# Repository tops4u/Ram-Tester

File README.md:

# Ram-Tester
**Fast, open-source DIY tester for vintage DRAM/SRAM** — auto-detects the
chip type, runs every test, gives a clear good/bad in seconds.

[GPL v3] [Firmware 5.1.2] · C64 · Amiga · Atari · ST · Apple II · Spectrum

## What this project is
A fast, open-source DIY RAM tester for vintage RAM chips used in C64, Amiga, Atari, and other retro computers. Built around a 16MHz ATmega328P on a custom PCB, it tests memory thoroughly in seconds and supports a wide range of chip types with optional OLED feedback.

<br/>

**As featured on:**

- [***Jan Beta***](https://www.youtube.com/watch?v=iQYF2-FwuoI) (Aug 2026): "The best Arduino Tester (so far)"
- [***Adrians Digital Basement II***](https://youtu.be/9QQ8ZqHPRVQ?&t=2573) (May 2026): "This is freaking awesome"
- [***Hackaday***](https://hackaday.com/2025/12/08/cheap-and-aggressive-dram-chip-tester/) (Dec 2025): "Cheap and Aggressive DRAM Chip Tester"
- [***Elektor Magazine***](https://www.elektormagazine.com/news/open-source-diy-ram-tester) (Dec 2025): "Ram-Tester Is an Open-Source DIY Solution for Retro Computer RAM"

---

## Why this tester?
- **No chip knowledge needed** – Set the pin count via DIP switch — the tester auto-detects the chip type and runs all tests automatically. No selecting algorithms, no choosing the right socket, no menus, no datasheet lookups. Grab a chip, plug it in, get a result.
- **Fast** – Full test in under 8 seconds for a 41256. Test a whole tray of chips in minutes.
- **Thorough** – While other testers require you to choose between test modes, this one runs them all: March-B address decoder test, memory patterns, crosstalk, retention time, CAS-before-RAS refresh, fast page mode, static column mode, short detection (VCC, GND and pin-to-pin).
- **Practical** – Broken is broken. You get a clear good/bad result because a DRAM chip can't be repaired anyway.
- **Safe** – Short-circuit protection, current limiting via resettable fuse, short detection against VCC, GND and between pins. Self-test mode included.
- **Fully Open Source** – Hardware, firmware, schematics. No black box.

---

## Key features
| Feature | Benefit |
|---------|---------|
| 20-pin ZIP socket on board | Direct test of 256K × 4 and 1M × 4 ZIP DRAMs without an adapter |
| Optional ZIP/SOJ adapter | Adds 1M × 1 ZIP and 41256 ZIP support, plus SOJ sockets for 18- and 20-pin SOJ RAMs <sup>1)</sup> |
| Optional OLED display or LED blink codes | Full text feedback or minimal hardware setup |
| Self-test mode | Verify the hardware for defects like short circuits or broken solder joints |

<sup>1)</sup> The 1M × 1 ZIP pinout differs from the 256K × 4 / 1M × 4 ZIP pinout, so these chips cannot use the on-board ZIP socket. See [Supported DRAM types](#supported-dram-types-speed-with-current-firmware-version).

---

## Supported DRAM types (speed with current firmware version)

| Capacity | DIP | 20-pin ZIP | Static Column | Nibble Mode | Retention Time | Test Time |
|----------|-----|------------|---------------|-------------|----------------|-----------|
| 4 K × 1 | 4027 <sup>1)</sup> | – | – | – | 2 ms | 0.2 s |
| 16 K × 1 | 4816 | – | – | – | 2 ms | 0.7 s |
| 16 K × 1 | 4116 <sup>1)</sup> | – | – | – | 2 ms | 0.5 s |
| 16 K × 4 | 4416 | – | – | – | 4 ms | 1.7 s |
| 32 K × 1 | 3732 <sup>2)</sup> | – | – | – | 2/4 ms | 1.8 s |
| 32 K × 1 | 4532 <sup>2)</sup> | – | – | – | 2/4 ms | 1.8 s |
| 64 K × 1 | 4164 | – | – | – | 2/4 ms | 1.8 s |
| 64 K × 4 | 4464 | – | – | – | 4 ms | 5.2 s |
| 256 K × 1 | 41256 | adapter <sup>3)</sup> | – | 41257 | 4 ms | 7.5 s |
| 256 K × 4 | 44256 | on board | 44258 | – | 8 ms | 3.5 s |
| 1 M × 1 | 411000 / 511000 | adapter <sup>3)</sup> | – | – | 8 ms | 19.4 s |
| 1 M × 4 | 514400 | on board | 514402 | – | 16 ms | 12.0 s |

<sup>1)</sup> Requires the [4116 adapter board](Schematic/4116).<br/>
<sup>2)</sup> Half-good 4164 chips sold as 32K × 1 (OKI MSM3732 / TI TMS4532). Enabled by default since firmware 4.2.3. See [32K documentation](Docs/32K-Option) for details.<br/>
<sup>3)</sup> The 1M × 1 ZIP pinout differs from the 256K × 4 / 1M × 4 ZIP pinout, so 411000 / 511000 ZIP chips cannot be tested in the on-board ZIP socket. The separate ZIP/SOJ adapter provides the matching ZIP socket for 1M × 1 and 41256, plus two SOJ sockets for 20-pin and 18-pin SOJ RAMs.

**Static Column** means the RAM allows column changes while CAS is held low — faster than standard page mode. **Nibble Mode** delivers four consecutive bits from one column address.

## Supported SRAM types (speed with current firmware version)

| Capacity | DIP | Test Time |
|----------|-----|-----------|
| 1 K × 4 | 2114 <sup>1)</sup> | 0.4 s |

<sup>1)</sup> **WARNING:** 2114 SRAM needs to be inserted 180° rotated, with Pin 10 of the SRAM on the ZIF Pin 1 marking.

---

## Test procedure

1. Insert the device (16, 18 or 20 pins, DIP or ZIP). 1M × 1 ZIP, 41256 ZIP and SOJ chips go into the ZIP/SOJ adapter.
2. Set the DIP switch to match the pin count of your RAM. See the [operation manual](Docs) for the switch settings.
3. Connect USB power supply (or press RESET if already powered).
4. Read the result
   * OLED version: plain-text report on the display
   * LED-only version: green = pass, red = fail

There is a short YouTube video demonstrating the tester in action. <br/>
<br/>

---

## How does it test?
1. Shorts — checks whether any pin is shorted to GND, to VCC (5 V) or to another pin
2. Chip detection — detects whether a chip is present and identifies its type
3. Address line and decoder faults — March-B sequence applied to the address lines
4. Stuck cells and crosstalk — bidirectional checkerboards
5. Random patterns combined with retention time checks
6. CAS-before-RAS refresh counter function (if supported by the RAM)
7. All of the above use the appropriate access mode for the chip type: Fast Page Mode, Static Column, or Nibble Mode

### Test algorithm and March-B
The tester combines a March-B sequence with chip-specific stress tests.

**March-B for address decoding.** Address line and decoder faults are detected with a March-B sequence (R0W1, R1W0, ascending and descending) applied to a reduced address set that exercises every row and column address line individually. This catches shorted, open or stuck address lines and decoder aliasing systematically, without running a full cell-level march.

**Why not a full cell-level March-B?** For the fault classes that matter in practice, the combination above offers comparable coverage, and it adds what a full March-B leaves out:

- **Access modes:** A classic March-B accesses every cell individually (direct single-cell read/write). It does not exercise the full feature set of a RAM chip, such as Fast Page Mode, Static Column, Nibble Mode or CAS-before-RAS refresh. This tester tests every feature the chip supports.
- **Retention:** March-B runs in the microsecond range per access, so it cannot catch chips with weak retention that pass on paper yet fail under real refresh timing, which is where most age-related failures occur. Cell-level coverage here comes from bidirectional checkerboards and random patterns combined with real retention delays.
- **Test time:** A full cell-level March-B on large chips such as 1M × 1 or 1M × 4 is not feasible on an ATmega328P within a practical test time. The goal is a reliable result in seconds, not minutes.

| Aspect | This Tester | Full cell-level March-B |
| --- | --- | --- |
| Address line / decoder faults | ✅ March-B on address lines | ✅ |
| Stuck cells, 0→1 / 1→0 transitions | ✅ Checkerboard + random patterns | ✅ |
| Address sequence | ✅ Ascending + descending | ✅ Ascending + descending |
| Crosstalk / coupling | ✅ Bidirectional checkerboards | ✅ Systematic |
| VCC/GND short detection | ✅ Explicit, before test | ⚠️ Implicit only <sup>1)</sup> |
| Pin-to-pin short detection | ✅ Explicit, before test | ⚠️ Implicit only <sup>1)</sup> |
| Access modes | ✅ FPM, Static Column, Nibble Mode | ❌ Direct single-cell access only |
| CBR refresh | ✅ CAS-before-RAS test <sup>2)</sup> | ❌ Not covered <sup>3)</sup> |
| Real retention | ✅ 2–16 ms per chip spec | ❌ Not covered <sup>3)</sup> |
| Test time on ATmega328P | ✅ Seconds | ❌ Not practical for large chips |

<sup>1)</sup> a short makes the chip fail the march, but the fault is not identified as a short<br>
<sup>2)</sup> for RAMs with a refresh counter (41256 and newer)<br>
<sup>3)</sup> unless implemented outside of March-B

### A note on CMOS vs TTL voltage levels
Vintage DRAM chips were designed for TTL signal levels. The ATmega328P drives CMOS levels at 5 V — logic high is close to V<sub>CC</sub>, which is above what the original systems delivered. This means marginal chips that fail at true TTL thresholds may still pass on this tester (and most other microcontroller-based testers).
Some designs use 3.3 V controllers with 5 V-tolerant I/O to get closer to TTL levels, but the ATmega328P does not support this operating mode. In practice, virtually no consumer DRAM tester on the market operates at true TTL levels — this is a fundamental limitation of the approach, not specific to this project. For definitive TTL-level testing, dedicated vintage test equipment (e.g. Advantest, Agilent) operating at calibrated thresholds would be needed.

### Experimental: Retention Time Measurement firmware
An alternative, experimental firmware measures how long the chip actually keeps its data without refresh, determined by its weakest cell, instead of giving a pass/fail result. It is currently available for 4164, 4464 and 44256/514256. Flashing it temporarily replaces the regular tester firmware. See [Software](Software) for details.

---

## Build or buy — the choice is yours

**Buy ready-made:** [Amibay](https://www.amibay.com/threads/memory-tester.2450230/) · [Lectronz](https://lectronz.com/products/ram-tester) · [eBay](https://www.ebay.ch/itm/136743995188) · [Tindie](https://www.tindie.com/products/reusecircuit/ram-tester-for-2114-4116-4164-41256-441000-514256/)

**Build it yourself (DIY):** Available as a beginner-friendly through-hole (THT) version or a compact SMD version. Order PCBs at [PCBWay (TH)](https://www.pcbway.com/project/shareproject/Ram_Tester_ThruHole_Version_93863356.html) or use the provided Gerber files from the [Schematic](Schematic) folder.

---

## Documentation

* [**Operation manual**](Docs) – test procedure, error codes, self-test and troubleshooting
* [**Software / Firmware**](Software) – firmware variants, flashing instructions
* [**Schematic**](Schematic) – KiCad project and Gerber files (THT and SMD)
* [**Changelog**](changelog.md) – firmware version history
* [**Compatibility**](compatibility.md) – manufacturer cross-reference and system DRAM/SRAM usage

---

## Building or selling your own units

You're welcome to build, modify and even sell your own Ram-Testers — that's the
point of open hardware. In return, the license asks you to keep it open:

- **It stays open-source.** Boards you distribute or sell remain under
  CERN-OHL-S v2 (hardware) and GPL v3 (firmware). No closing the design, no
  proprietary fork.
- **Pass on the source.** If you sell or give away boards, make the complete
  design files for *your* version — including any changes you made — available
  under the same license.
- **Keep the credit and the link.** Leave the copyright and license notices
  intact and keep the source location — https://github.com/tops4u/Ram-Tester/ —
  visible, on the board silkscreen where practicable (CERN-OHL-S §4).
- **Don't strip attribution.** Selling it as your own closed product, or
  removing the notices, is not permitted.
- **Article description.** For online platforms you need to include:
  Creator, link to the source files (this GitHub repo) and licence.

In short: build it, improve it, sell it — just keep it open and point people
back here. If unsure, open a Discussion and ask.

---

## Contributing

Pull requests, issues and forks are welcome.
Questions: GitHub Discussions or contact **tops4u** on AmiBay.

Open-source hardware (CERN-OHL-S v2) and firmware (GPL v3) – use at your own risk.

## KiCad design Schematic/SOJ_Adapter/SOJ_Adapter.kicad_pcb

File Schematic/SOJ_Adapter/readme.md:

# SOJ Aapter

This Adapter add 2 SOJ 26 Sockets which allows for testing of 514256/514400 Style RAM and 511000/411000 RAM in SOJ Packages.

It also adds 2 ZIP Sockets, one for 511000/411000 RAM in ZIP Package and the other for 41256 RAM in ZIP Package.

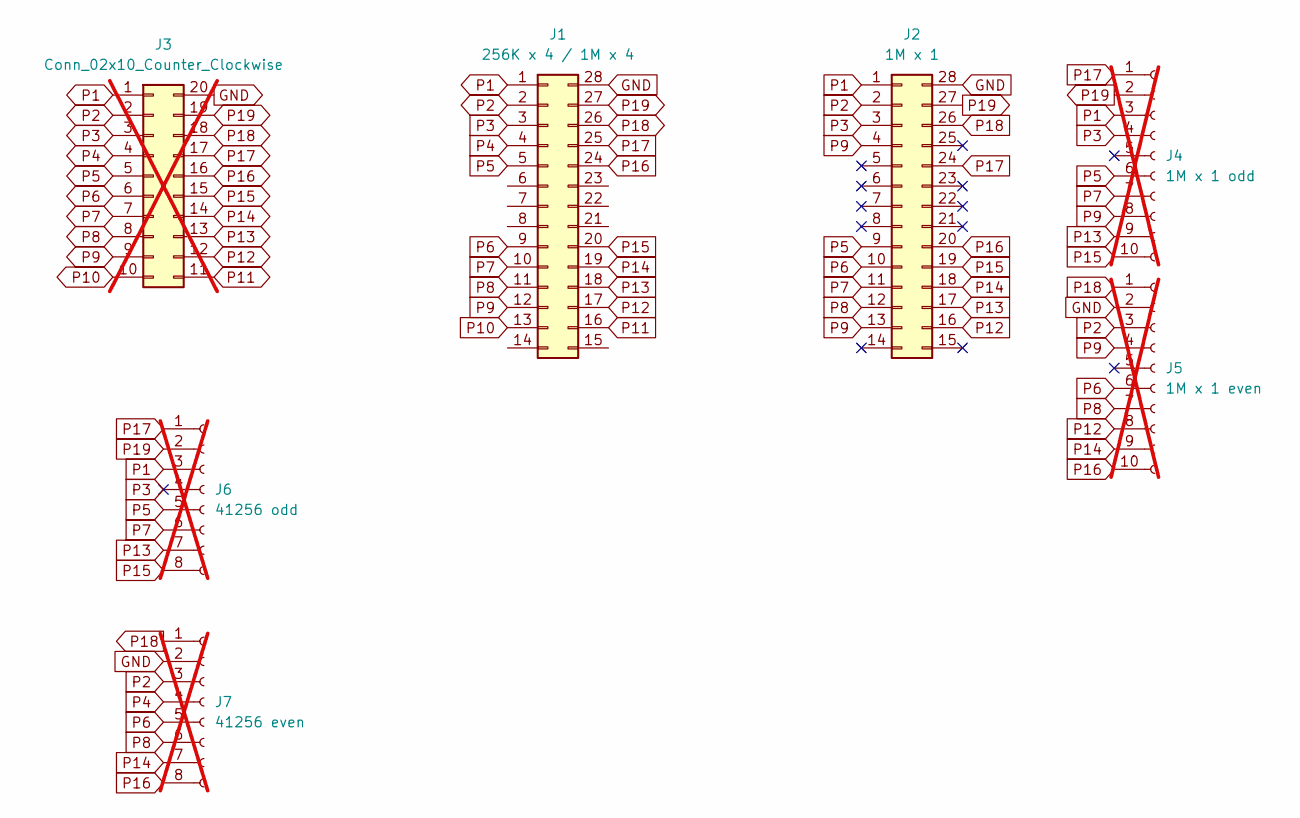
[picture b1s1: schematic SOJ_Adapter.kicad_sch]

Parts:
J1: 256K x 4 / 1M x 4; SOJ-28_7.62x18.415mm_P1.27mm
J2: 1M x 1; SOJ-28_7.62x18.415mm_P1.27mm
J3: Conn_02x10_Counter_Clockwise; DIP-20_W7.62mm; not fitted
J4: 1M x 1 odd; PinHeader_1x10_P2.54mm_Vertical; not fitted
J5: 1M x 1 even; PinHeader_1x10_P2.54mm_Vertical; not fitted
J6: 41256 odd; PinHeader_1x08_P2.54mm_Vertical; not fitted
J7: 41256 even; PinHeader_1x08_P2.54mm_Vertical; not fitted

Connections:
GND: J1.28, J2.28, J3.20, J5.2, J7.2
P1: J1.1, J2.1, J3.1, J4.3, J6.3
P2: J1.2, J2.2, J3.2, J5.3, J7.3
P3: J1.3, J2.3, J3.3, J4.4, J6.4
P4: J1.4, J3.4, J7.4
P5: J1.5, J2.9, J3.5, J4.6, J6.5
P6: J1.9, J2.10, J3.6, J5.6, J7.5
P7: J1.10, J2.11, J3.7, J4.7, J6.6
P8: J1.11, J2.12, J3.8, J5.7, J7.6
P9: J1.12, J2.4, J2.13, J3.9, J4.8, J5.4
P10: J1.13, J3.10
P11: J1.16, J3.11
P12: J1.17, J2.16, J3.12, J5.8
P13: J1.18, J2.17, J3.13, J4.9, J6.7
P14: J1.19, J2.18, J3.14, J5.9, J7.7
P15: J1.20, J2.19, J3.15, J4.10, J6.8
P16: J1.24, J2.20, J3.16, J5.10, J7.8
P17: J1.25, J2.24, J3.17, J4.1, J6.1
P18: J1.26, J2.26, J3.18, J5.1, J7.1
P19: J1.27, J2.27, J3.19, J4.2, J6.2

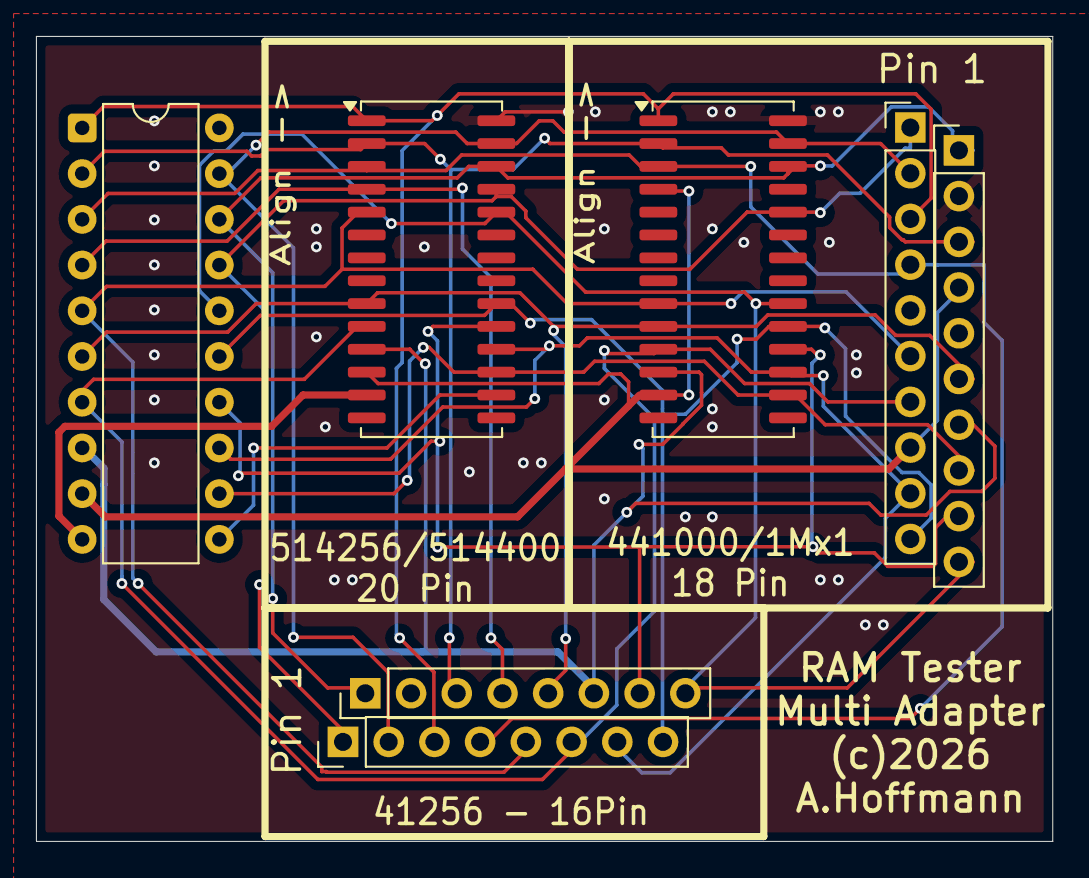
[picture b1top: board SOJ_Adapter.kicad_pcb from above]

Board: 2 copper layers, 56.5 x 44.7 mm, 7 parts (0 on the bottom side), 20 nets.

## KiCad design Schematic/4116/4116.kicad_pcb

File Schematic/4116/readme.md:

# 4116 Adapter

This is the adapter board for testing **4116** and **4027** RAM chips. These chips require −5 V and +12 V supply voltages that the main tester board does not provide.

> **Note:** You need firmware version **3.x.x or higher** to use this adapter!

---

## Why is it so complicated and expensive?

The RAM Tester was never originally designed to support 4116 RAM — this feature was added later due to popular demand.
When designing the adapter, I wanted to make sure it would be both easy to use and safe. That's why I included LEDs to indicate when all necessary voltages are present, as 4116 RAM can be very sensitive to missing or incorrect voltages.
I also added latch-up protection for the ICL7660 chip, which could otherwise lock up and overheat. Instead of simply using an off-the-shelf boost converter — which would have been far cheaper — I decided to design my own. This custom design limits current to 80 mA in case of a short circuit, whereas many off-the-shelf units can deliver up to 2 A, posing a risk of damage.
So yes, there are cheaper solutions out there, but they often come with trade-offs. It's entirely up to you whether you want to reuse this design or not.

---

## Important Notice

This circuit uses a **voltage inverter (ICL7660)**. As the name suggests, it inverts the supplied voltage.

- Example: if your USB power supply provides **+6 V**, the inverter will output **−6 V**.
- This exceeds the safe operating range of the **4116 RAM**:
  - Most RAM chips tolerate up to **+6.5 V**.
  - The 4116, however, only tolerates up to **−5.5 V**.

### Measuring the voltage

To ensure your power supply is behaving correctly, measure the voltage at the **16-pin ZIF socket** while it is unpopulated:

- Measure between **Pin 16 (GND)** and **Pin 1 (−5 V)**.
- The voltage must be between **−4.5 V** and **−5.5 V**.

---

## LED Indicators

The onboard LEDs will go off to indicate whether there is a short circuit on the **−5 V** or **+12 V** lines.

- If a short is detected, **remove the RAM immediately**.
- The adapter board can tolerate a permanent short:
  - Max current: **≈30 mA** on the −5 V line
  - Max current: **≈80 mA** on the +12 V line (version 3.4 introduced an additional 30 mA resettable fuse)

However, this still results in more than **1 W of power dissipation**, which will heat up the components significantly.

---

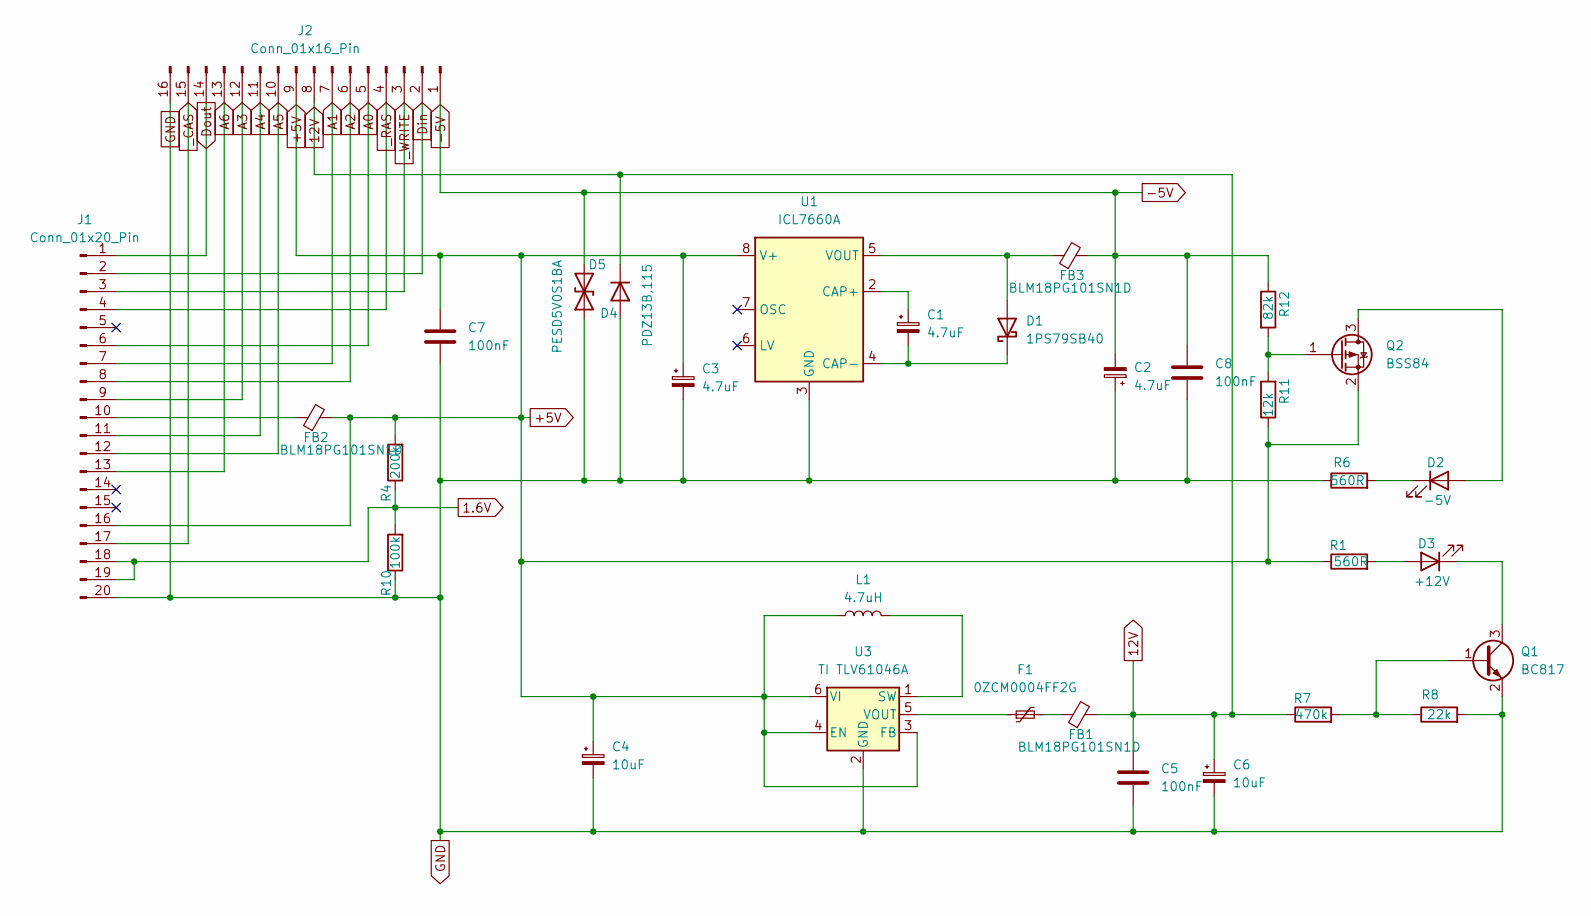
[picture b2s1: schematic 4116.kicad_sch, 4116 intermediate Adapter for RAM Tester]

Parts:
C1, C2, C3: 4.7uF; C_1206_3216Metric
C4, C6: 10uF; C_1206_3216Metric
C5, C7, C8: 100nF; C_0603_1608Metric
D1: 1PS79SB40; D_SOD-523
D2: -5V; LED_0603_1608Metric
D3: +12V; LED_0603_1608Metric
D4: PDZ13B,115; D_SOD-123F
D5: PESD5V0S1BA; D_SOD-323
F1: 0ZCM0004FF2G; Fuse_0603_1608Metric
FB1, FB2, FB3: BLM18PG101SN1D; L_0603_1608Metric_Pad1.05x0.95mm_HandSolder
J1: Conn_01x20_Pin; DIP-20_W7.62mm_1
J2: Conn_01x16_Pin; DIP-16_W7.62mm_1
L1: 4.7uH; L_1008_2520Metric
Q1: BC817; SOT-23
Q2: BSS84; SOT-23
R1, R6: 560R; R_0603_1608Metric
R4: 200k; R_0603_1608Metric
R7: 470k; R_0603_1608Metric
R8: 22k; R_0603_1608Metric
R10: 100k; R_0603_1608Metric
R11: 12k; R_0603_1608Metric
R12: 82k; R_0603_1608Metric
U1: ICL7660A; SOIC-8_3.9x4.9mm_P1.27mm
U3: TI TLV61046A; SOT-23-6

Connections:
1.6V: J1.18, J1.19, R4.1, R10.2
12V: C5.1, C6.1, D4.1 (K), FB1.2, J2.8, R7.1
+5V: C3.1, C4.1, C7.1, FB2.2, J1.16, J2.9, L1.1, Q2.2 (S), R1.1, R4.2, R11.1, U1.8 (V+), U3.3 (FB), U3.4 (EN), U3.6 (VI)
-5V: C2.2, C8.1, D5.2 (A2), FB3.2, J2.1, R12.1
A0: J1.6, J2.5
A1: J1.7, J2.7
A2: J1.8, J2.6
A3: J1.9, J2.12
A4: J1.11, J2.11
A5: J1.12, J2.10
A6: J1.13, J2.13
Din: J1.2, J2.2
Dout: J1.1, J2.14
GND: C2.1, C3.2, C4.2, C5.2, C6.2, C7.2, C8.2, D4.2 (A), D5.1 (A1), J1.20, J2.16, Q1.2 (E), R6.1, R8.2, R10.1, U1.3 (GND), U3.2 (GND)
unnamed: D1.2 (A), FB3.1, U1.5 (VOUT)
unnamed: C1.2, D1.1 (K), U1.4 (CAP-)
unnamed: D2.2 (A), Q2.3 (D)
unnamed: D2.1 (K), R6.2
unnamed: D3.2 (A), R1.2
unnamed: D3.1 (K), Q1.3 (C)
unnamed: F1.2, FB1.1
unnamed: FB2.1, J1.10
unnamed: Q1.1 (B), R7.2, R8.1
unnamed: Q2.1 (G), R11.2, R12.2
unnamed: C1.1, U1.2 (CAP+)
unnamed: L1.2, U3.1 (SW)
unnamed: F1.1, U3.5 (VOUT)
_CAS: J1.17, J2.15
_RAS: J1.4, J2.4
_WRITE: J1.3, J2.3

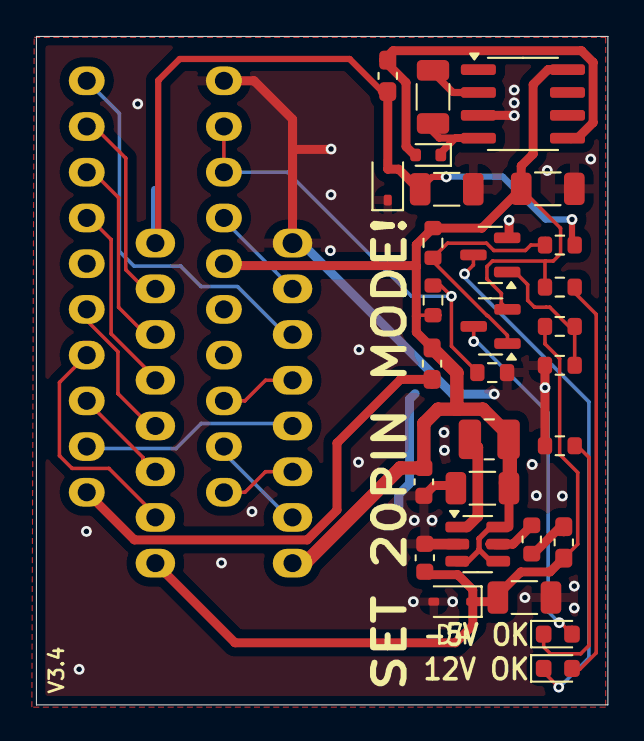
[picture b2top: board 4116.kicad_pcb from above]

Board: 2 copper layers, 31.7 x 37.1 mm, 32 parts (1 on the bottom side), 30 nets.

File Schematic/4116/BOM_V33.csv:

Designation;Qty;Description/Value;Footprint;
C1, C2, C3;3;4.7uF;1206;
C4, C6;2;10uF;1206;
C5, C7;2;100nF;0603;
D1;1;Shottky Diode;SOD-523;
D2, D3;2;LED Green;0603;
L1;1;4.7uH;1008;
Q1;1;BC817;SOT-23;
Q2;1;BSS84;SOT-23;
R1, R6;2;R560;0603;
R10;1;100k;0603;
R11;1;12k;0603;
R12;1;88.7k;0603;
R4;1;R200k;0603;
R7;1;R470k;0603;
R8;1;22k;0603;
U1;1;ICL7660ACBAZA;8-SOIC;
U3;1;TLV61046ADBVR;SOT-23-6;

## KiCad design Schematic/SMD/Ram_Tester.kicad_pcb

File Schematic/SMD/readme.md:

# SMD Version

This is the mixed SMD/through-hole version of the RAM Tester. SMD components are used for the main circuit; the ZIF socket, ZIP socket, DIP switch and pin headers are through-hole.

## Files in this folder

| File | Description |
|------|-------------|
| `Schematic_SMD.pdf` | Schematic as PDF for reference |
| `Ram_Tester.kicad_sch` / `.kicad_pcb` / `.kicad_pro` | KiCad 9 source files |
| `Ram_TesterSMD_v2.1.zip` | Gerber files for PCB manufacturing |

**Notes:**
- J1 (display) and J2 (ICSP) are pin headers, not SMD — solder them as through-hole.
- R1 and R6 are LED current limitors. The values above work with the Kingbright dual LED. If you substitute a different LED (e.g. from AliExpress), R6 may need to be 500–560 Ω depending on forward voltage.

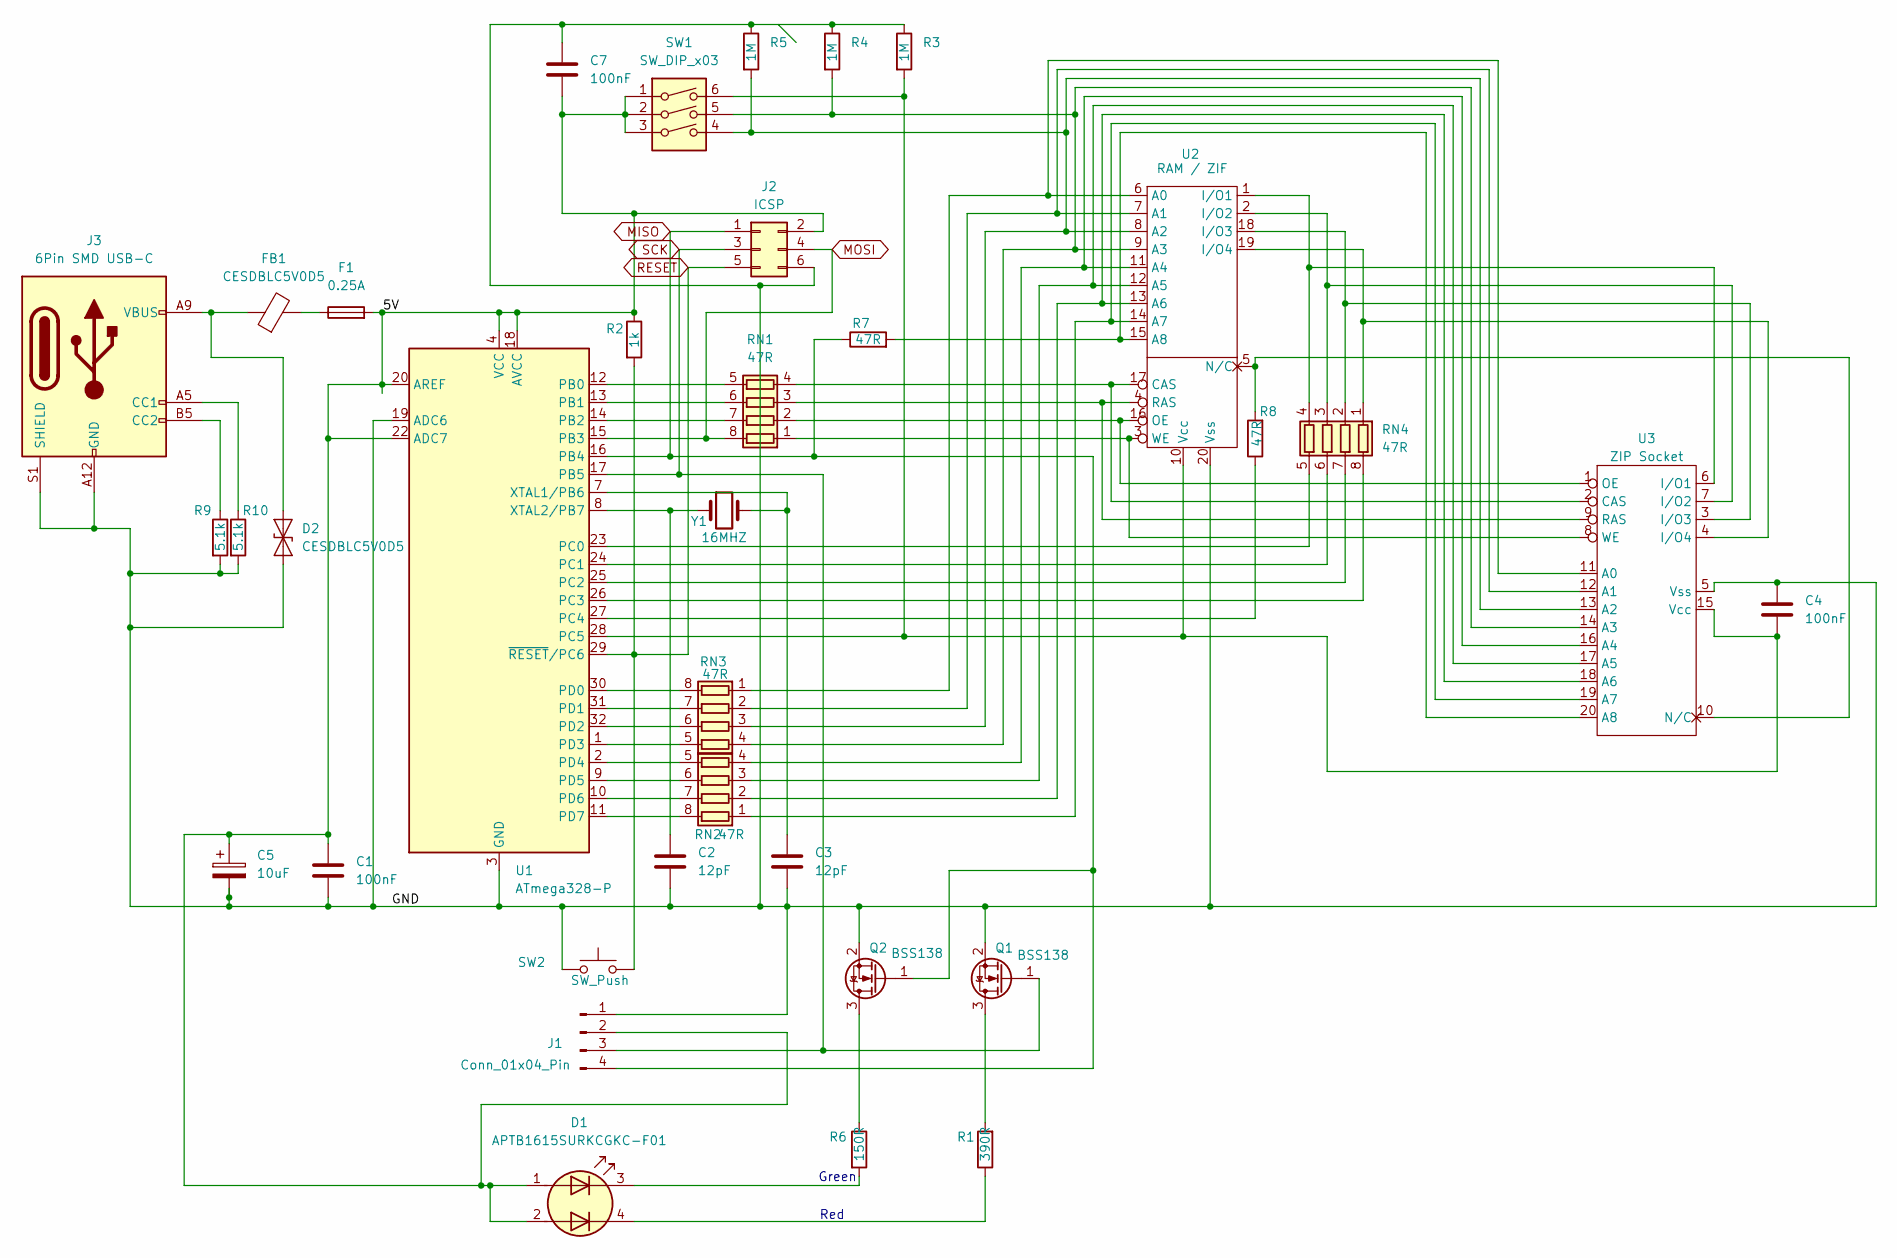
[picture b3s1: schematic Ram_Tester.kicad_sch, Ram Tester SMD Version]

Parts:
C1, C4, C7: 100nF; C_0603_1608Metric_Pad1.08x0.95mm_HandSolder; PartNr 06036C104MAZ2A
C2, C3: 12pF; C_0603_1608Metric; PartNr 0603CG120F500NT
C5: 10uF; C_1206_3216Metric; PartNr T491A106K006AT7280
D1: APTB1615SURKCGKC-F01; LED_SMD_RG_AKAK
D2: CESDBLC5V0D5; D_SOD-923
F1: 0.25A; Fuse_1206_3216Metric; PartNr SMD1206P025TF
FB1: CESDBLC5V0D5; L_0603_1608Metric
J1: Conn_01x04_Pin; PinHeader_1x04_P2.54mm_Vertical
J2: ICSP; PinHeader_2x03_P2.54mm_Vertical
J3: 6Pin SMD USB-C; USB_C_Receptacle_GCT_USB4125-xx-x-0190_6P_TopMnt_Horizontal; PartNr USB4125-GF-A-0190
Q1, Q2: BSS138; SOT-23; PartNr BSS138
R1: 390R; R_0603_1608Metric; PartNr RC0603FR-07390RL
R2: 1k; R_0603_1608Metric; PartNr RT0603FRE071KL
R3, R4, R5: 1M; R_0603_1608Metric; PartNr AC0603FR-131ML
R6: 150R; R_0603_1608Metric; PartNr RT0603FRE13150RL
R7, R8: 47R; R_0603_1608Metric; PartNr RC-ML08W471JT
R9, R10: 5.1k; R_0603_1608Metric; PartNr RT0603FRD075K1L
RN1, RN2, RN3, RN4: 47R; R_Array_Concave_4x0603; PartNr RC-ML08W471JT
SW1: SW_DIP_x03; SW_DIP_SPSTx03_Slide_9.78x9.8mm_W7.62mm_P2.54mm
SW2: SW_Push; SW_Push_1P1T_NO_6x6mm_H9.5mm; PartNr K2-1808SN-A4SW-01
U1: ATmega328-P; TQFP-32_7x7mm_P0.8mm; PartNr ATMEGA328P-AU
U2: RAM / ZIF; DIP-20_W7.62mm_LongPads
U3: ZIP Socket; ZIP-20
Y1: 16MHZ; Crystal_SMD_5032-2Pin_5.0x3.2mm; PartNr TXM16.000M2503FDCE-O00T

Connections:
/5V: C1.1, C5.1, C7.2, D1.1 (A1), D1.2 (A2), F1.2, J1.2, J2.2, R2.1, SW1.1, SW1.2, SW1.3, U1.4 (VCC), U1.6 (VCC), U1.18 (AVCC), U1.20 (AREF), U1.22 (ADC7)
/GND: C1.2, C2.2, C3.2, C4.1, C5.2, C7.1, D2.2 (A2), J1.1, J2.6, J3.A12 (GND), J3.B12 (GND), J3.S1 (SHIELD), Q1.2 (S), Q2.2 (S), R3.1, R4.1, R5.1, R9.2, R10.2, SW2.1, U1.3 (GND), U1.5 (GND), U1.19 (ADC6), U1.21 (GND), U2.20 (Vss), U3.5 (Vss)
MISO: J1.4, J2.1, Q2.1 (G), R7.1, U1.16 (PB4)
MOSI: J2.4, RN1.8 (R1.2), U1.15 (PB3)
unnamed: D1.3 (K1), R6.2
unnamed: D1.4 (K2), R1.1
unnamed: D2.1 (A1), FB1.1, J3.A9 (VBUS), J3.B9 (VBUS)
unnamed: F1.1, FB1.2
unnamed: J3.A5 (CC1), R10.1
unnamed: J3.B5 (CC2), R9.1
unnamed: Q1.3 (D), R1.2
unnamed: Q2.3 (D), R6.1
unnamed: RN1.1 (R1.1), U2.3 (WE), U3.8 (WE)
unnamed: RN1.2 (R2.1), U2.16 (OE), U3.1 (OE)
unnamed: RN1.7 (R2.2), U1.14 (PB2)
unnamed: RN1.3 (R3.1), U2.4 (RAS), U3.9 (RAS)
unnamed: RN1.6 (R3.2), U1.13 (PB1)
unnamed: RN1.4 (R4.1), U2.17 (CAS), U3.2 (CAS)
unnamed: RN1.5 (R4.2), U1.12 (PB0)
unnamed: RN2.1 (R1.1), U2.14 (A7), U3.19 (A7)
unnamed: RN2.8 (R1.2), U1.11 (PD7)
unnamed: RN2.2 (R2.1), U2.13 (A6), U3.18 (A6)
unnamed: RN2.7 (R2.2), U1.10 (PD6)
unnamed: RN2.3 (R3.1), U2.12 (A5), U3.17 (A5)
unnamed: RN2.6 (R3.2), U1.9 (PD5)
unnamed: RN2.4 (R4.1), U2.11 (A4), U3.16 (A4)
unnamed: RN2.5 (R4.2), U1.2 (PD4)
unnamed: RN3.1 (R1.1), U2.6 (A0), U3.11 (A0)
unnamed: RN3.8 (R1.2), U1.30 (PD0)
unnamed: RN3.2 (R2.1), U2.7 (A1), U3.12 (A1)
unnamed: RN3.7 (R2.2), U1.31 (PD1)
unnamed: R5.2, RN3.3 (R3.1), SW1.4, U2.8 (A2), U3.13 (A2)
unnamed: RN3.6 (R3.2), U1.32 (PD2)
unnamed: R4.2, RN3.4 (R4.1), SW1.5, U2.9 (A3), U3.14 (A3)
unnamed: RN3.5 (R4.2), U1.1 (PD3)
unnamed: RN4.1 (R1.1), U2.19 (I/O4), U3.4 (I/O4)
unnamed: RN4.8 (R1.2), U1.26 (PC3)
unnamed: RN4.2 (R2.1), U2.18 (I/O3), U3.3 (I/O3)
unnamed: RN4.7 (R2.2), U1.25 (PC2)
unnamed: RN4.3 (R3.1), U2.2 (I/O2), U3.7 (I/O2)
unnamed: RN4.6 (R3.2), U1.24 (PC1)
unnamed: RN4.4 (R4.1), U2.1 (I/O1), U3.6 (I/O1)
unnamed: RN4.5 (R4.2), U1.23 (PC0)
unnamed: R8.1, U1.27 (PC4)
unnamed: C4.2, R3.2, SW1.6, U1.28 (PC5), U2.10 (Vcc), U3.15 (Vcc)
unnamed: C3.1, U1.7 (XTAL1/PB6), Y1.2
unnamed: C2.1, U1.8 (XTAL2/PB7), Y1.1
unnamed: R7.2, U2.15 (A8), U3.20 (A8)
unnamed: R8.2, U2.5 (N/C), U3.10 (N/C)
RESET: J2.5, R2.2, SW2.2, U1.29 (~RESET/PC6)
SCK: J1.3, J2.3, Q1.1 (G), U1.17 (PB5)

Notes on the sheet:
Green
Red

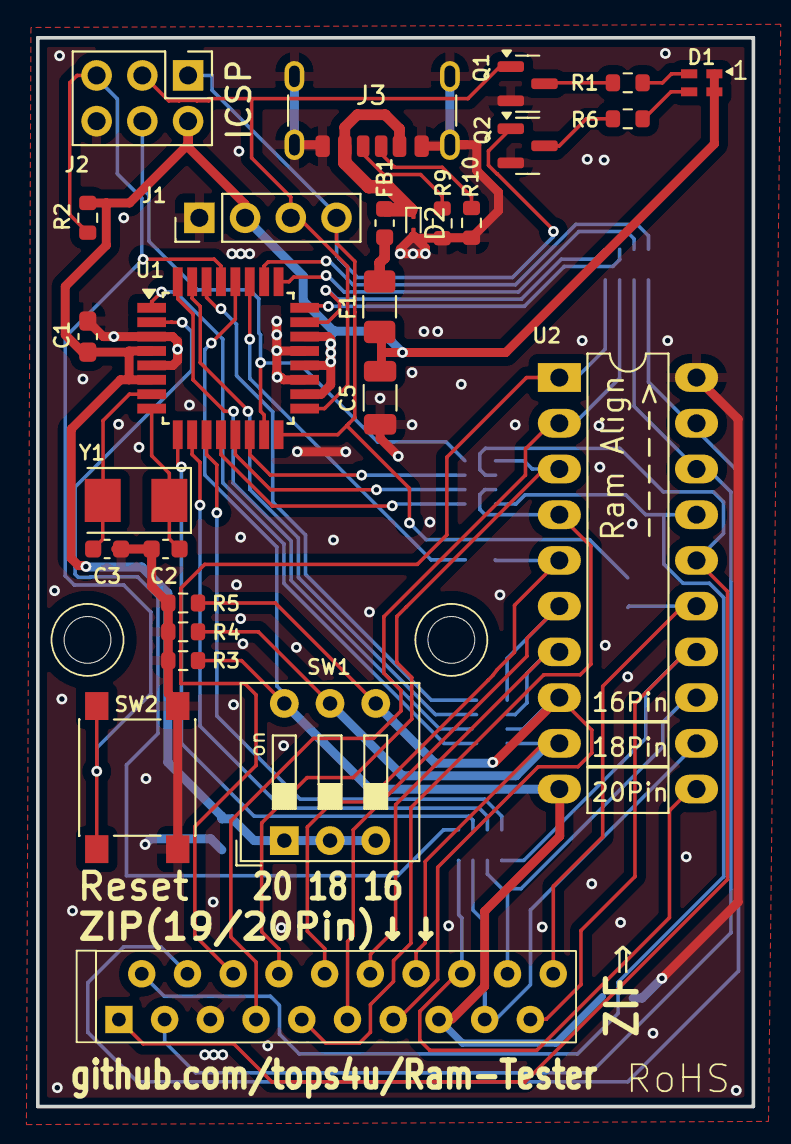
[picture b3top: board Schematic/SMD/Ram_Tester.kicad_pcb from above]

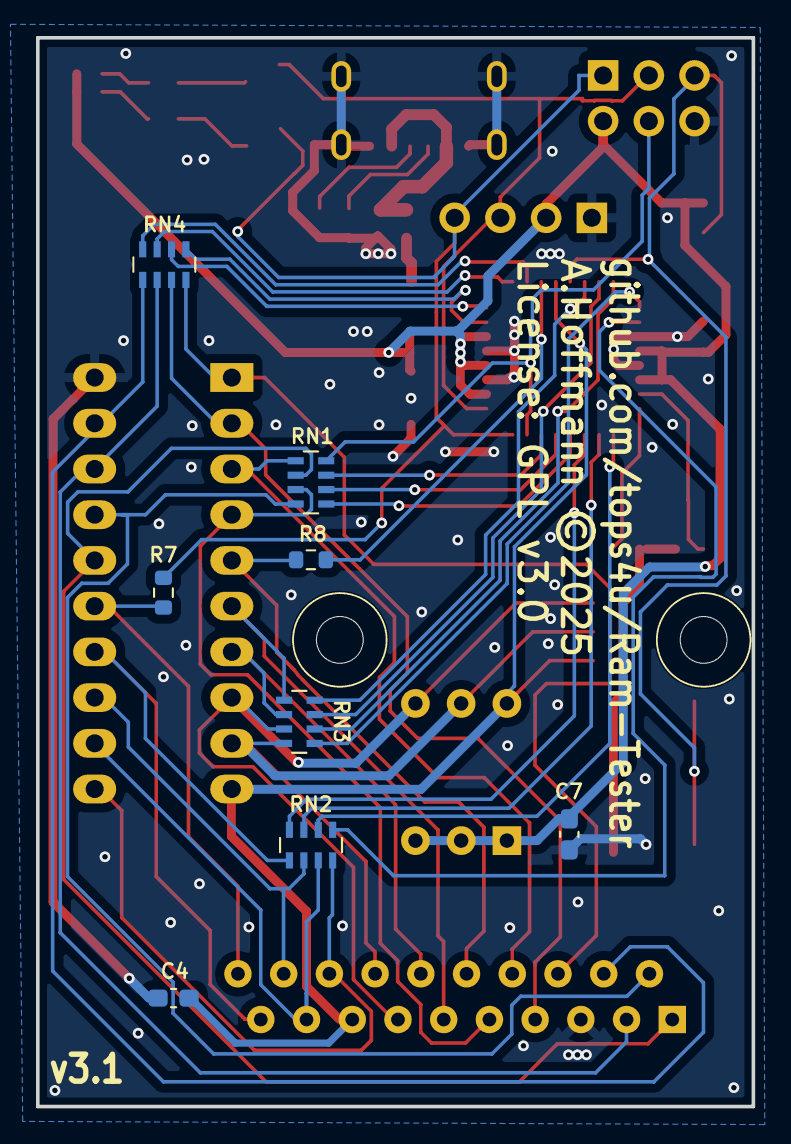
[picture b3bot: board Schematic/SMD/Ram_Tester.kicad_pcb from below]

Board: 2 copper layers, 39.8 x 59.4 mm, 35 parts (8 on the bottom side), 51 nets.

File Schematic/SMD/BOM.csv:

Id,Designator,Footprint,Quantity,Designation,Manufacturer,Part Number,Type,Notes
6,"C3,C2",0603,2,15pF,kemet,C0603C150K5GAC,SMD,
3,C5,1206,1,10uF,kyocera avx,T491A106K006AT7280,SMD,
9,"C7,C4,C1",0605,3,100nF,kyocera avx,06036C104MAZ2A,SMD,
7,D1,0805 Duo LED,1,LED_Dual_AAKK,Kingbright,APTB1615SURKCGKC-F01,SMD,
13,F1,1206,1,0.5A,Eaton electronics,PTS12066V050,SMD,
1,J1,PinHeader_1x04_P2.54mm_Vertical,0,Conn_01x04_Pin,-,-,THT,Do not mount
18,J2,PinHeader_2x03_P2.54mm_Vertical,0,ICSP,-,-,THT,Do not mount
17,J3,USB_C_Receptacle_GCT_USB4125-xx-x-0190_6P_TopMnt_Horizontal,1,USB_C_Receptacle_PowerOnly_6P,shou han,TYPE-C 6P(073),SMD,
11,"Q1,Q2",SOT-23,2,BSS138,Onsemi,BSS138,SMD,
2,R1,0603,1,390R,yageo,RT0603FRE13390RL,SMD,
10,"R10,R9",0603,2,5.1k,yageo,RT0603FRD075K1L,SMD,
15,R2,0603,1,1k,yageo,RT0603FRE071KL,SMD,
4,"R4,R5,R3",0603,3,1M,yageo,AC0603FR-131ML,SMD,
5,R6,0603,1,150R,yageo,RT0603FRE13150RL,SMD,
21,"R8,R7",0603,2,47R,yageo,RT0603DRD0747RL,SMD,
22,"RN2,RN3,RN4,RN1",4x0603,4,47R,SEI,RAVF164DJT47R0,SMD,
12,SW1,DIP-6_W7.62mm,1,SW_DIP_x03,-,-,THT,Do not mount
14,SW2,TLZWLA_Button,1,SW_Push,-,-,SMD,
8,U1,TQFP-32,1,ATmega328-P,Microchip Technology,ATMEGA328P-AU,SMD,
20,U2,DIP-20_W7.62mm_LongPads,0,RAM / ZIF,-,-,THT,Do not mount
19,U3,ZIP-20,0,ZIP Socket,-,-,THT,Do not mount
16,Y1,5032,1,16MHZ,CTS Electronics Components,445I32C16M00000,SMD,

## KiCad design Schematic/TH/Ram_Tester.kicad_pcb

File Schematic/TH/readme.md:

# Through-Hole (THT) Version

The through-hole version is designed for easy hand-soldering. It is functionally identical to the SMD version but with a few differences:

- No ESD/EMI protection components
- Micro-USB instead of USB-C (6-pin USB-C THT connectors are hard to source)

## Board revisions

### v3.0 
- Fixes two minor errors from v2.0
- Moves the OLED display to the centre of the board so the ICSP header remains accessible even with the display soldered in place
- Files: `Gerber_TH_v3.zip`, KiCad source files in this folder

## BOM

The bill of materials is available as `BOM_TH_RamTester.csv` in this folder.

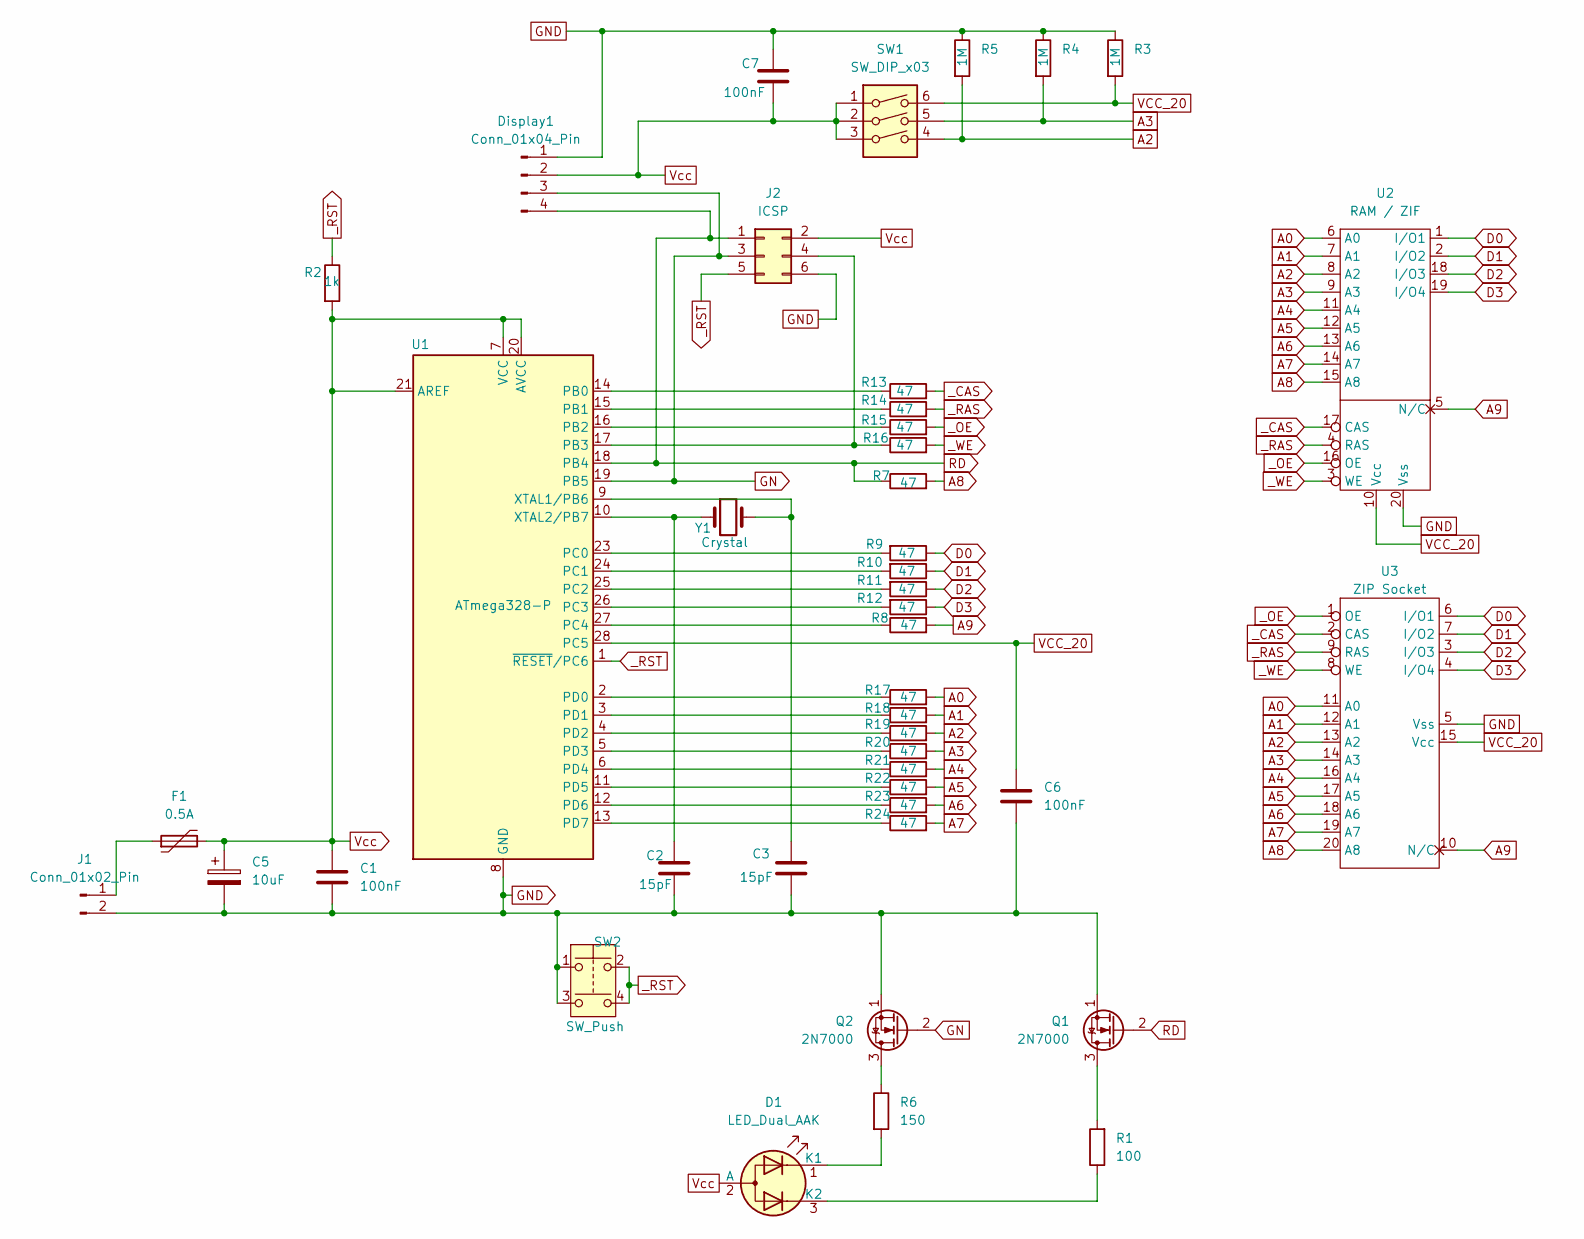
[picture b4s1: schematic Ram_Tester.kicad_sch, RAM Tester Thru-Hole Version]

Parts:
C1, C6, C7: 100nF; C_Disc_D4.3mm_W1.9mm_P5.00mm
C2, C3: 15pF; C_Disc_D4.3mm_W1.9mm_P5.00mm
C5: 10uF; CP_Radial_D4.0mm_P2.00mm
D1: LED_Dual_AAK; LED_D5.0mm-3
Display1: Conn_01x04_Pin; PinHeader_1x04_P2.54mm_Vertical
F1: 0.5A; Fuse_Littelfuse_395Series
J1: Conn_01x02_Pin; MicroUSB PowerOnly
J2: ICSP; PinHeader_2x03_P2.54mm_Vertical
Q1, Q2: 2N7000; TO-92_Inline
R1: 100; R_Axial_DIN0204_L3.6mm_D1.6mm_P7.62mm_Horizontal
R2: 1k; R_Axial_DIN0204_L3.6mm_D1.6mm_P7.62mm_Horizontal
R3, R4, R5: 1M; R_Axial_DIN0204_L3.6mm_D1.6mm_P7.62mm_Horizontal
R6: 150; R_Axial_DIN0204_L3.6mm_D1.6mm_P7.62mm_Horizontal
R7, R8, R9, R10, R11, R12, R13, R14, R15, R16, R17, R18, R19, R20, R21, R22, R23, R24: 47; R_Axial_DIN0204_L3.6mm_D1.6mm_P7.62mm_Horizontal
SW1: SW_DIP_x03; SW_DIP_SPSTx03_Slide_9.78x9.8mm_W7.62mm_P2.54mm
SW2: SW_Push; SW_TH_Tactile_Omron_B3F-10xx
U1: ATmega328-P; DIP-28_W7.62mm
U2: RAM / ZIF; DIP-20_W7.62mm_LongPads
U3: ZIP Socket; ZIP-20
Y1: Crystal; Crystal_HC49-U_Vertical

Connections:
A0: R17.2, U2.6 (A0), U3.11 (A0)
A1: R18.2, U2.7 (A1), U3.12 (A1)
A2: R5.2, R19.2, SW1.4, U2.8 (A2), U3.13 (A2)
A3: R4.2, R20.2, SW1.5, U2.9 (A3), U3.14 (A3)
A4: R21.2, U2.11 (A4), U3.16 (A4)
A5: R22.2, U2.12 (A5), U3.17 (A5)
A6: R23.2, U2.13 (A6), U3.18 (A6)
A7: R24.2, U2.14 (A7), U3.19 (A7)
A8: R7.2, U2.15 (A8), U3.20 (A8)
A9: R8.2, U2.5 (N/C), U3.10 (N/C)
D0: R9.1, U2.1 (I/O1), U3.6 (I/O1)
D1: R10.1, U2.2 (I/O2), U3.7 (I/O2)
D2: R11.1, U2.18 (I/O3), U3.3 (I/O3)
D3: R12.1, U2.19 (I/O4), U3.4 (I/O4)
GN: Display1.3, J2.3, Q2.2 (G), U1.19 (PB5); also elsewhere on the board
GND: C1.2, C2.2, C3.2, C5.2, C6.2, C7.1, Display1.1, J1.2, J2.6, Q1.1 (S), Q2.1 (S), R3.1, R4.1, R5.1, SW2.1, SW2.3, U1.8 (GND), U1.22 (GND), U2.20 (Vss), U3.5 (Vss); also elsewhere on the board
unnamed: D1.1 (K1), R6.2
unnamed: D1.3 (K2), R1.1
unnamed: F1.1, J1.1
unnamed: J2.4, R16.1, U1.17 (PB3)
unnamed: Q1.3 (D), R1.2
unnamed: Q2.3 (D), R6.1
unnamed: R13.1, U1.14 (PB0)
unnamed: R14.1, U1.15 (PB1)
unnamed: R15.1, U1.16 (PB2)
unnamed: R9.2, U1.23 (PC0)
unnamed: R10.2, U1.24 (PC1)
unnamed: R11.2, U1.25 (PC2)
unnamed: R12.2, U1.26 (PC3)
unnamed: R8.1, U1.27 (PC4)
unnamed: R17.1, U1.2 (PD0)
unnamed: R18.1, U1.3 (PD1)
unnamed: R19.1, U1.4 (PD2)
unnamed: R20.1, U1.5 (PD3)
unnamed: R21.1, U1.6 (PD4)
unnamed: R22.1, U1.11 (PD5)
unnamed: R23.1, U1.12 (PD6)
unnamed: R24.1, U1.13 (PD7)
unnamed: C3.1, U1.9 (XTAL1/PB6), Y1.2
unnamed: C2.1, U1.10 (XTAL2/PB7), Y1.1
RD: Display1.4, J2.1, Q1.2 (G), R7.1, U1.18 (PB4); also elsewhere on the board
VCC_20: C6.1, R3.2, SW1.6, U1.28 (PC5), U2.10 (Vcc), U3.15 (Vcc)
Vcc: C1.1, C5.1, C7.2, D1.2 (A), Display1.2, F1.2, J2.2, R2.2, SW1.1, SW1.2, SW1.3, U1.7 (VCC), U1.20 (AVCC), U1.21 (AREF); also elsewhere on the board
_CAS: R13.2, U2.17 (CAS), U3.2 (CAS)
_OE: R15.2, U2.16 (OE), U3.1 (OE)
_RAS: R14.2, U2.4 (RAS), U3.9 (RAS)
_RST: J2.5, R2.1, SW2.2, SW2.4, U1.1 (~RESET/PC6)
_WE: R16.2, U2.3 (WE), U3.8 (WE)

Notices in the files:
Schematic/Ram_Tester.kicad_pcb:
A.Hoffmann ©2024
License: GPL v3.0
Schematic/SMD/Ram_Tester.kicad_pcb:
A.Hoffmann ©2025
